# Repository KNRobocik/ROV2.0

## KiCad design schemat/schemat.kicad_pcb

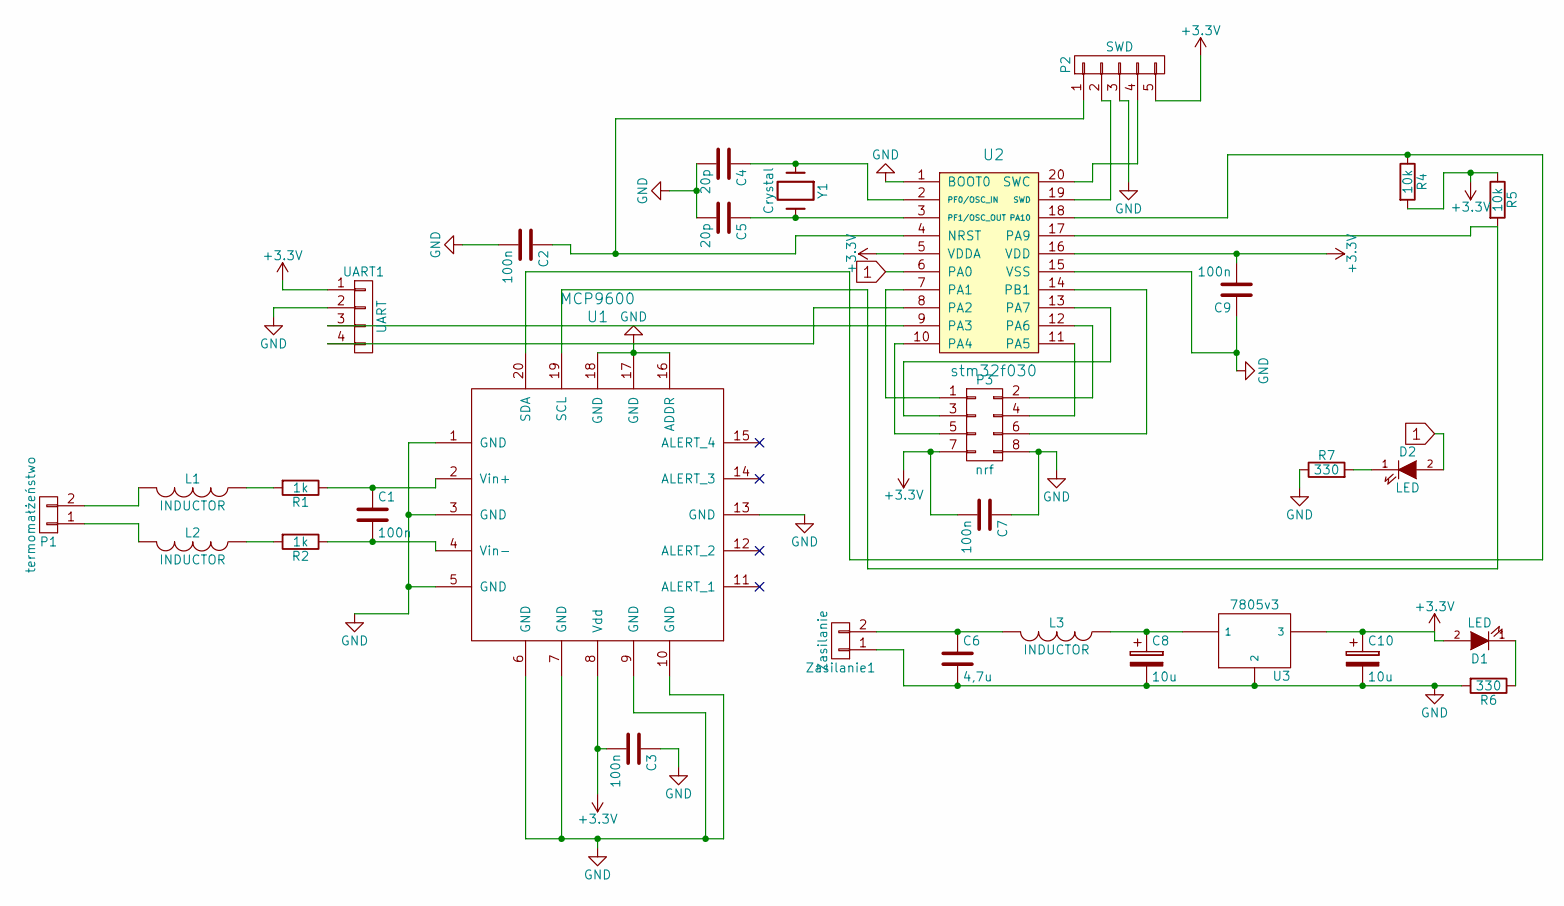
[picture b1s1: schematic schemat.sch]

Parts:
C1, C2, C3, C7, C9: 100n; C_0805_HandSoldering
C4, C5: 20p; C_0805_HandSoldering
C6: 4,7u; C_0805_HandSoldering
C8, C10: 10u; c_elec_4x4.5
D1, D2: LED; LED_1206
L1, L2, L3: INDUCTOR; inductor_smd_0805
P1: termomałżeństwo; mkds_1,5-2
P2: SWD; bb02-hy05a
P3: nrf; bb02-hp08
R1, R2: 1k; R_0805_HandSoldering
R4, R5: 10k; R_0805_HandSoldering
R6, R7: 330; R_0805_HandSoldering
U1: MCP9600; mcp9600_dp
U2: stm32f030; tssop-20
U3: 7805v3; TO-220_Neutral123_Vertical
UART1: UART; bb02-hy04a
Y1: Crystal; Crystal_HC49-SD_SMD
Zasilanie1: Zasilanie; mkds_1,5-2

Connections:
1: D2.2 (A), U2.6 (PA0)
+3V3: C3.2, C7.2, C9.2, C10.1, D1.2 (A), P2.5, P3.7, R4.2, R5.1, U1.8 (Vdd), U2.5 (VDDA), U2.16 (VDD), U3.3, UART1.1
unnamed: C1.1, R1.1, U1.2 (Vin+)
unnamed: C1.2, R2.1, U1.4 (Vin-)
unnamed: C2.1, P2.1, U2.4 (NRST)
unnamed: C4.1, U2.2 (PF0/OSC_IN), Y1.1
unnamed: C5.1, U2.3 (PF1/OSC_OUT), Y1.2
unnamed: C6.1, L3.2, Zasilanie1.2
unnamed: C8.1, L3.1, U3.1
unnamed: D1.1 (K), R6.1
unnamed: D2.1 (K), R7.2
unnamed: L1.1, R1.2
unnamed: L1.2, P1.2
unnamed: L2.1, R2.2
unnamed: L2.2, P1.1
unnamed: P2.2, U2.19 (SWD)
unnamed: P2.4, U2.20 (SWC)
unnamed: P3.1, U2.7 (PA1)
unnamed: P3.2, U2.12 (PA6)
unnamed: P3.3, U2.13 (PA7)
unnamed: P3.4, U2.11 (PA5)
unnamed: P3.5, U2.10 (PA4)
unnamed: P3.6, U2.14 (PB1)
unnamed: R4.1, U1.20 (SDA), U2.18 (PA10)
unnamed: R5.2, U1.19 (SCL), U2.17 (PA9)
unnamed: U2.9 (PA3), UART1.3

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
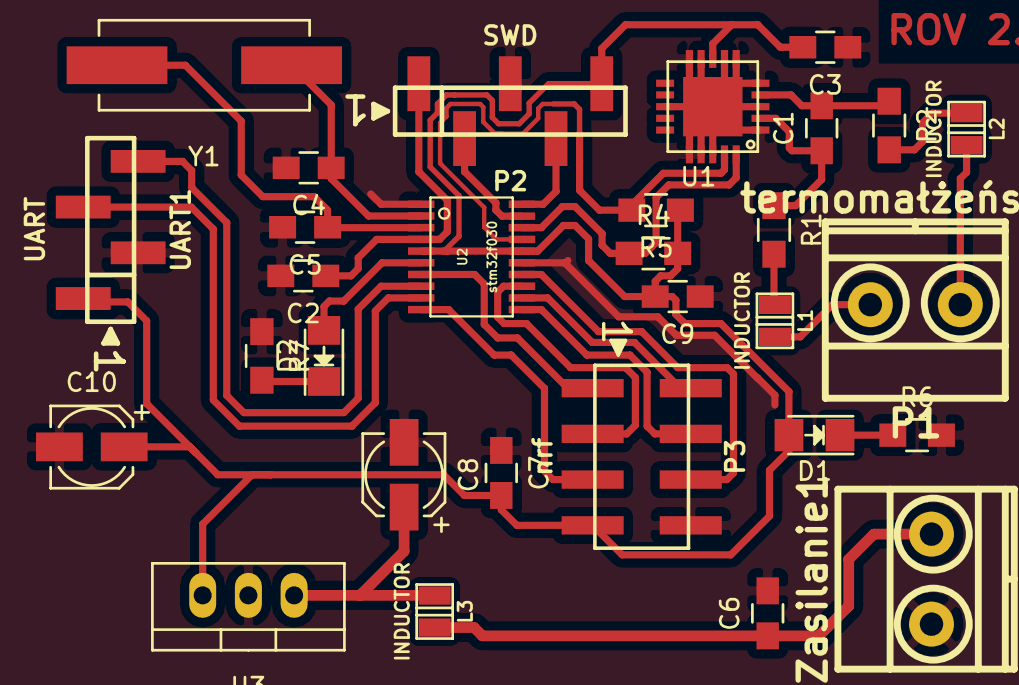
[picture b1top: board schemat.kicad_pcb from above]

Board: 2 copper layers, 30 parts (0 on the bottom side), 28 nets.

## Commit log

2016-11-30 Create BasicInterfejs
2016-11-30 Update BasicInterfejs
